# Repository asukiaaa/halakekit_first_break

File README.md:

# HaLakeKitFirstBreak
A KiCAD project for HaLakeKitFirst with using Arduino Pro Micro.

# Reference
(HaLakeKitFirst)[https://github.com/nyampass/HaLakeKitFirst-Library]

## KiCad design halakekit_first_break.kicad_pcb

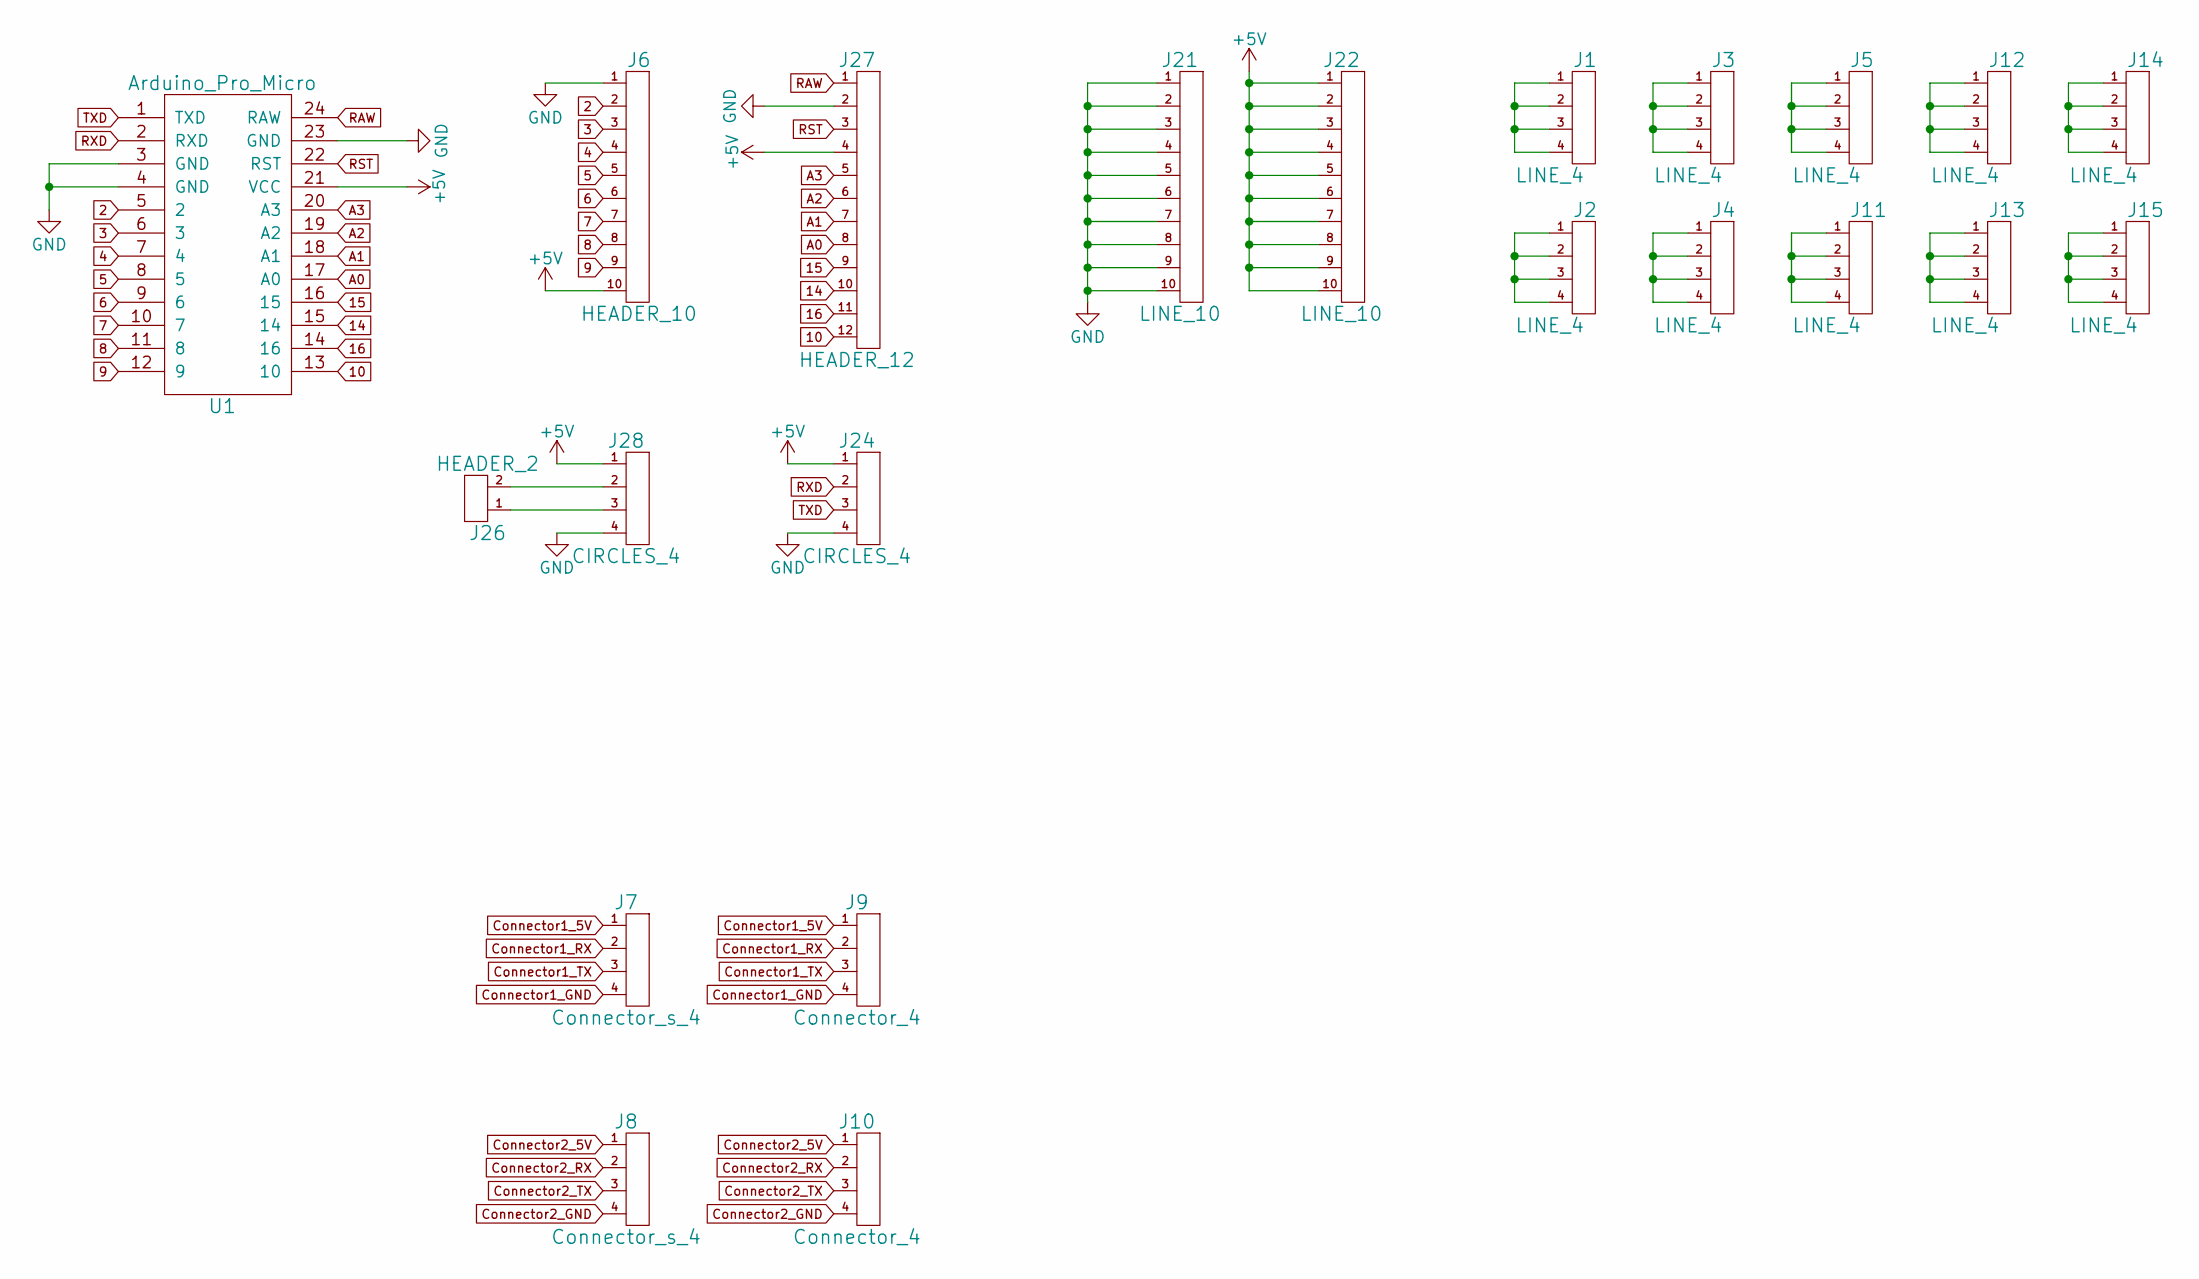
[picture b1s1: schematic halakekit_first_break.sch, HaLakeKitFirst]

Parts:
J1, J2, J3, J4, J5, J11, J12, J13, J14, J15: LINE_4; Pin_Header_Connect_1x04
J6: HEADER_10; Pin_Header_Straight_1x10
J7, J8: Connector_s_4; headers_s_4
J9, J10: Connector_4; Pin_Header_Straight_1x04
J21, J22: LINE_10; Pin_Header_Straight_1x10
J24, J28: CIRCLES_4; Pin_Header_Circle_1x04
J26: HEADER_2; Pin_Header_Straight_1x02
J27: HEADER_12; Pin_Header_Straight_1x12
U1: Arduino_Pro_Micro; Arduino Pro Micro

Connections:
2: J6.2, U1.5 (2)
3: J6.3, U1.6 (3)
4: J6.4, U1.7 (4)
5: J6.5, U1.8 (5)
6: J6.6, U1.9 (6)
7: J6.7, U1.10 (7)
8: J6.8, U1.11 (8)
9: J6.9, U1.12 (9)
10: J27.12, U1.13 (10)
14: J27.10, U1.15 (14)
15: J27.9, U1.16 (15)
16: J27.11, U1.14 (16)
+5V: J6.10, J22.1, J22.2, J22.3, J22.4, J22.5, J22.6, J22.7, J22.8, J22.9, J22.10, J24.1, J27.4, J28.1, U1.21 (VCC)
A0: J27.8, U1.17 (A0)
A1: J27.7, U1.18 (A1)
A2: J27.6, U1.19 (A2)
A3: J27.5, U1.20 (A3)
Connector1_5V: J7.1, J9.1
Connector1_GND: J7.4, J9.4
Connector1_RX: J7.2, J9.2
Connector1_TX: J7.3, J9.3
Connector2_5V: J8.1, J10.1
Connector2_GND: J8.4, J10.4
Connector2_RX: J8.2, J10.2
Connector2_TX: J8.3, J10.3
GND: J6.1, J21.1, J21.2, J21.3, J21.4, J21.5, J21.6, J21.7, J21.8, J21.9, J21.10, J24.4, J27.2, J28.4, U1.3 (GND), U1.4 (GND), U1.23 (GND)
unnamed: J1.1, J1.2, J1.3, J1.4
unnamed: J2.1, J2.2, J2.3, J2.4
unnamed: J3.1, J3.2, J3.3, J3.4
unnamed: J4.1, J4.2, J4.3, J4.4
unnamed: J5.1, J5.2, J5.3, J5.4
unnamed: J11.1, J11.2, J11.3, J11.4
unnamed: J12.1, J12.2, J12.3, J12.4
unnamed: J13.1, J13.2, J13.3, J13.4
unnamed: J14.1, J14.2, J14.3, J14.4
unnamed: J15.1, J15.2, J15.3, J15.4
unnamed: J26.1, J28.3
unnamed: J26.2, J28.2
RAW: J27.1, U1.24 (RAW)
RST: J27.3, U1.22 (RST)
RXD: J24.2, U1.2 (RXD)
TXD: J24.3, U1.1 (TXD)

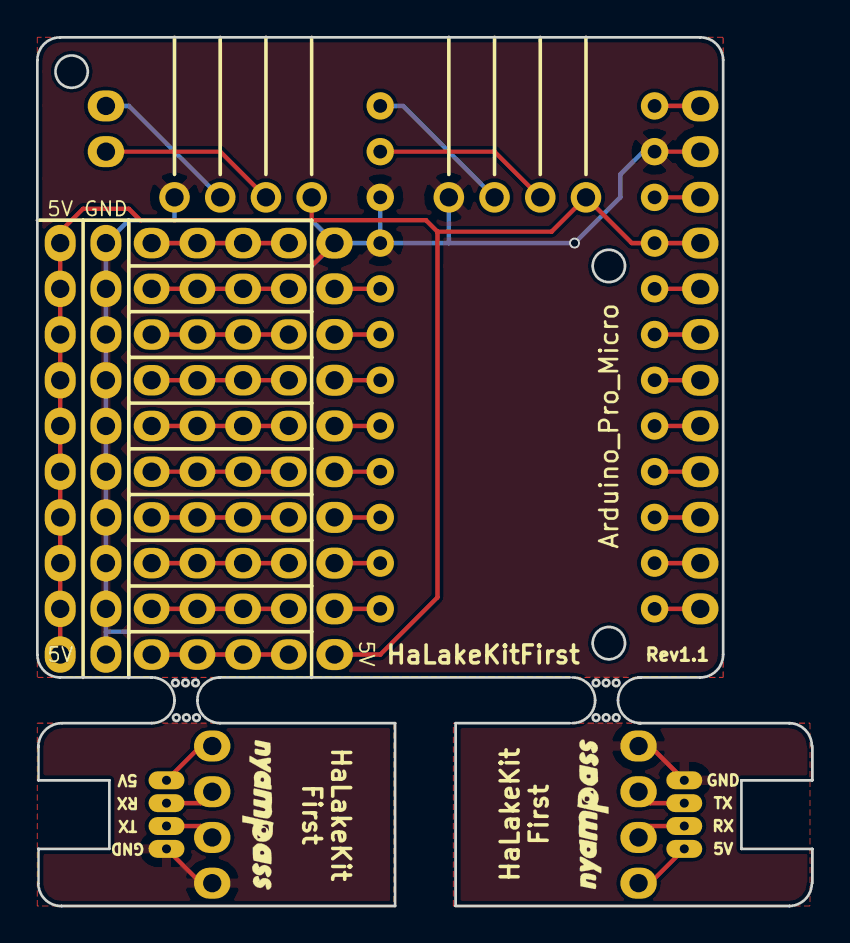
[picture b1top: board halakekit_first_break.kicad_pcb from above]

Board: 2 copper layers, 43.1 x 48.3 mm, 22 parts (0 on the bottom side), 42 nets.

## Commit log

2017-02-25 Change size of holl and connector footprint larger
2017-02-25 Update plot files
2017-02-26 Add image and readme
2017-03-12 Add components to readme
